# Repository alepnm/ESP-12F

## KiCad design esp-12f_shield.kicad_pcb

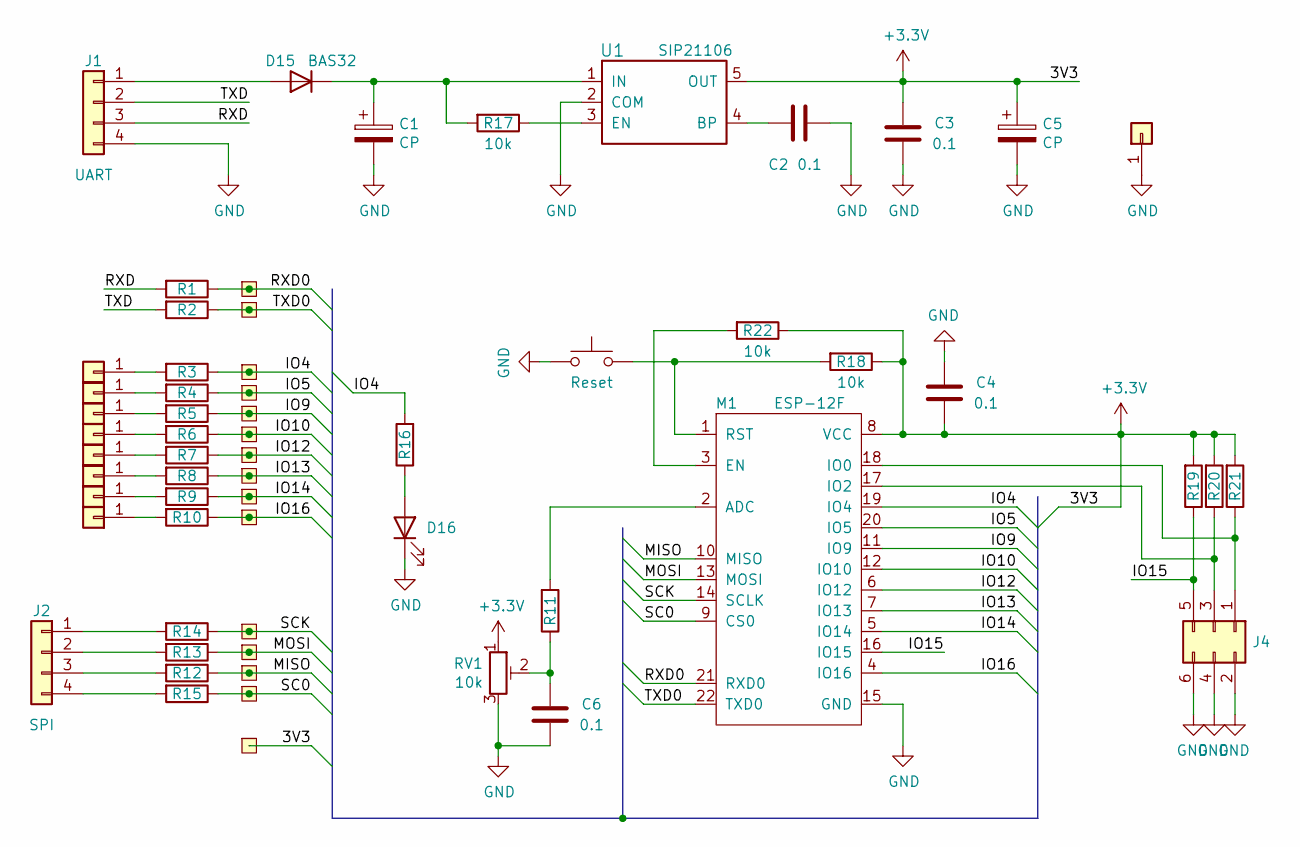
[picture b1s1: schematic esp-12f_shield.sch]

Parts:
C1: CP; CP_Radial_D6.3mm_P2.50mm
C2, C3, C4, C6: 0.1; C_0805_2012Metric
C5: CP; CP_Radial_D5.0mm_P2.50mm
D1, D2, D3, D4, D5, D6, D7, D8, D9, D10, D11, D12, D13, D14: Sold_Pad_small; TestPoint_Pad_1.5x1.5mm
D15: BAS32; D_MiniMELF
D16: LED; LED_0805_2012Metric_Pad1.15x1.40mm_HandSolder
J1: UART; JST_EH_B4B-EH-A_1x04_P2.50mm_Vertical
J2: SPI; JST_EH_B4B-EH-A_1x04_P2.50mm_Vertical
J3: Sold_Pad_small; TestPoint_Pad_1.5x1.5mm
J4: Conn_02x03_Odd_Even; PinHeader_2x03_P2.54mm_Vertical
J5, J6, J7, J8, J9, J10, J11, J12, J13: Conn_01x01; SolderWirePad_1x01_Drill0.8mm
M1: ESP-12F; esp-12f_module
R1, R2, R3, R4, R5, R6, R7, R8, R9, R10, R11, R12, R13, R14, R15, R16: 100; R_0805_2012Metric_Pad1.15x1.40mm_HandSolder
R17, R18, R19, R20, R21, R22: 10k; R_0805_2012Metric_Pad1.15x1.40mm_HandSolder
RV1: 10k; Potentiometer_Bourns_3296Y_Vertical
SW1: Reset; SW_DIP_SPSTx01_Slide_6.7x4.1mm_W7.62mm_P2.54mm_LowProfile
U1: SIP21106; SOT-23-5

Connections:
+3V3: C3.2, C4.1, C5.1, J3.1, M1.8 (VCC), R18.1, R19.2, R20.2, R21.2, R22.1, RV1.1, U1.5 (OUT); also elsewhere on the board
/IO4: D3.1, M1.19 (IO4), R3.1, R16.2
/IO5: D4.1, M1.20 (IO5), R4.1
/IO9: D5.1, M1.11 (IO9), R5.1
/IO10: D6.1, M1.12 (IO10), R6.1
/IO12: D7.1, M1.6 (IO12), R7.1
/IO13: D8.1, M1.7 (IO13), R8.1
/IO14: D9.1, M1.5 (IO14), R9.1
/IO15: J4.5, M1.16 (IO15), R19.1
/IO16: D10.1, M1.4 (IO16), R10.1
/MISO: D11.1, M1.10 (MISO), R12.1
/MOSI: D12.1, M1.13 (MOSI), R13.1
/RXD: J1.3, R1.2
/RXD0: D1.1, M1.21 (RXD0), R1.1
/SC0: D14.1, M1.9 (CS0), R15.1
/SCK: D13.1, M1.14 (SCLK), R14.1
/TXD: J1.2, R2.2
/TXD0: D2.1, M1.22 (TXD0), R2.1
GND: C1.2, C2.1, C3.1, C4.2, C5.2, C6.1, D16.1 (K), J1.4, J4.2, J4.4, J4.6, J13.1, M1.15 (GND), RV1.3, SW1.1, U1.2 (COM); also elsewhere on the board
unnamed: C1.1, D15.1 (K), R17.2, U1.1 (IN)
unnamed: C2.2, U1.4 (BP)
unnamed: C6.2, R11.1, RV1.2
unnamed: D15.2 (A), J1.1
unnamed: D16.2 (A), R16.1
unnamed: J2.1, R14.2
unnamed: J2.2, R13.2
unnamed: J2.3, R12.2
unnamed: J2.4, R15.2
unnamed: J4.1, M1.18 (IO0), R21.1
unnamed: J4.3, M1.17 (IO2), R20.1
unnamed: J5.1, R3.2
unnamed: J6.1, R4.2
unnamed: J7.1, R5.2
unnamed: J8.1, R6.2
unnamed: J9.1, R7.2
unnamed: J10.1, R8.2
unnamed: J11.1, R9.2
unnamed: J12.1, R10.2
unnamed: M1.1 (RST), R18.2, SW1.2
unnamed: M1.2 (ADC), R11.2
unnamed: M1.3 (EN), R22.2
unnamed: R17.1, U1.3 (EN)

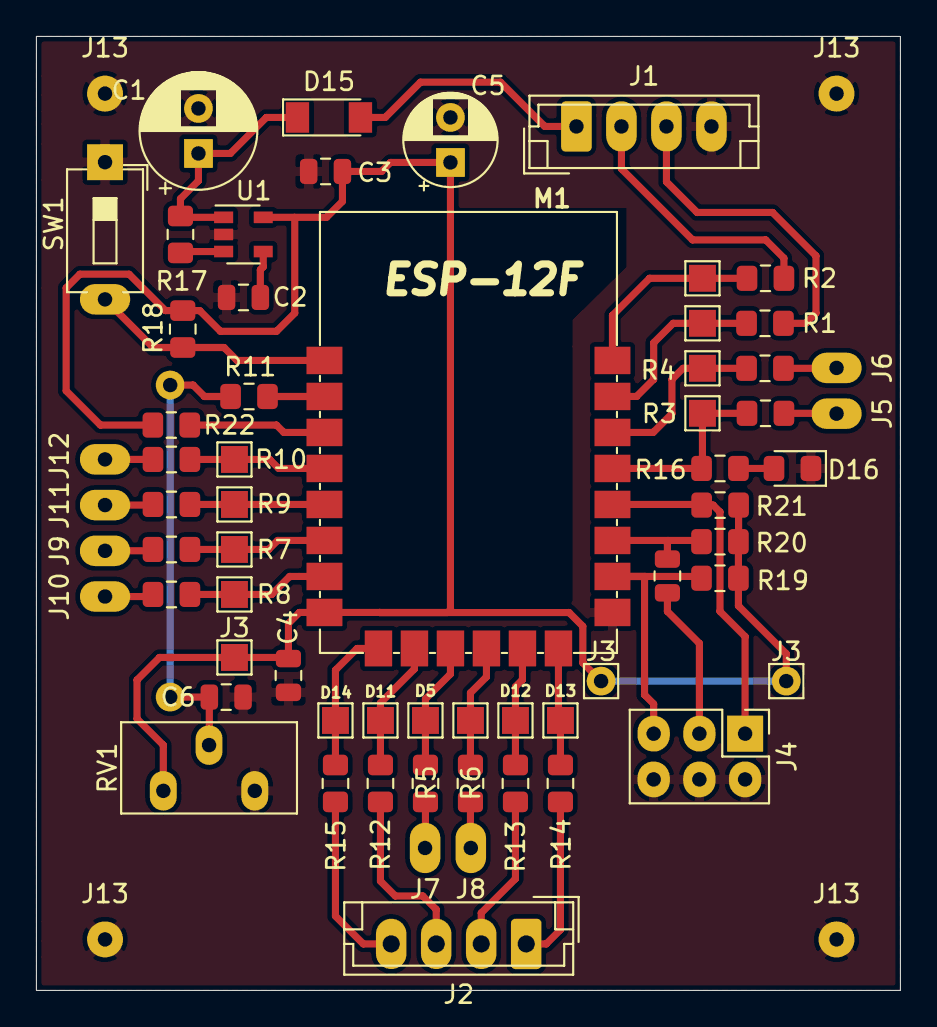
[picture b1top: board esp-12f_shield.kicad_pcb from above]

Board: 2 copper layers, 48.0 x 53.0 mm, 66 parts (0 on the bottom side), 42 nets.

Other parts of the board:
J3#2, J3#3: Sold_Pad_small; TestPoint_Pad_1.5x1.5mm
J13#2, J13#3, J13#4: Conn_01x01; SolderWirePad_1x01_Drill0.8mm

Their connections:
+3V3: J3#2.1, J3#3.1; also elsewhere on the board
GND: J13#2.1, J13#3.1, J13#4.1; also elsewhere on the board

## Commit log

2020-01-10 inicializavimas
2020-01-12 paruosta schema ir plokste
